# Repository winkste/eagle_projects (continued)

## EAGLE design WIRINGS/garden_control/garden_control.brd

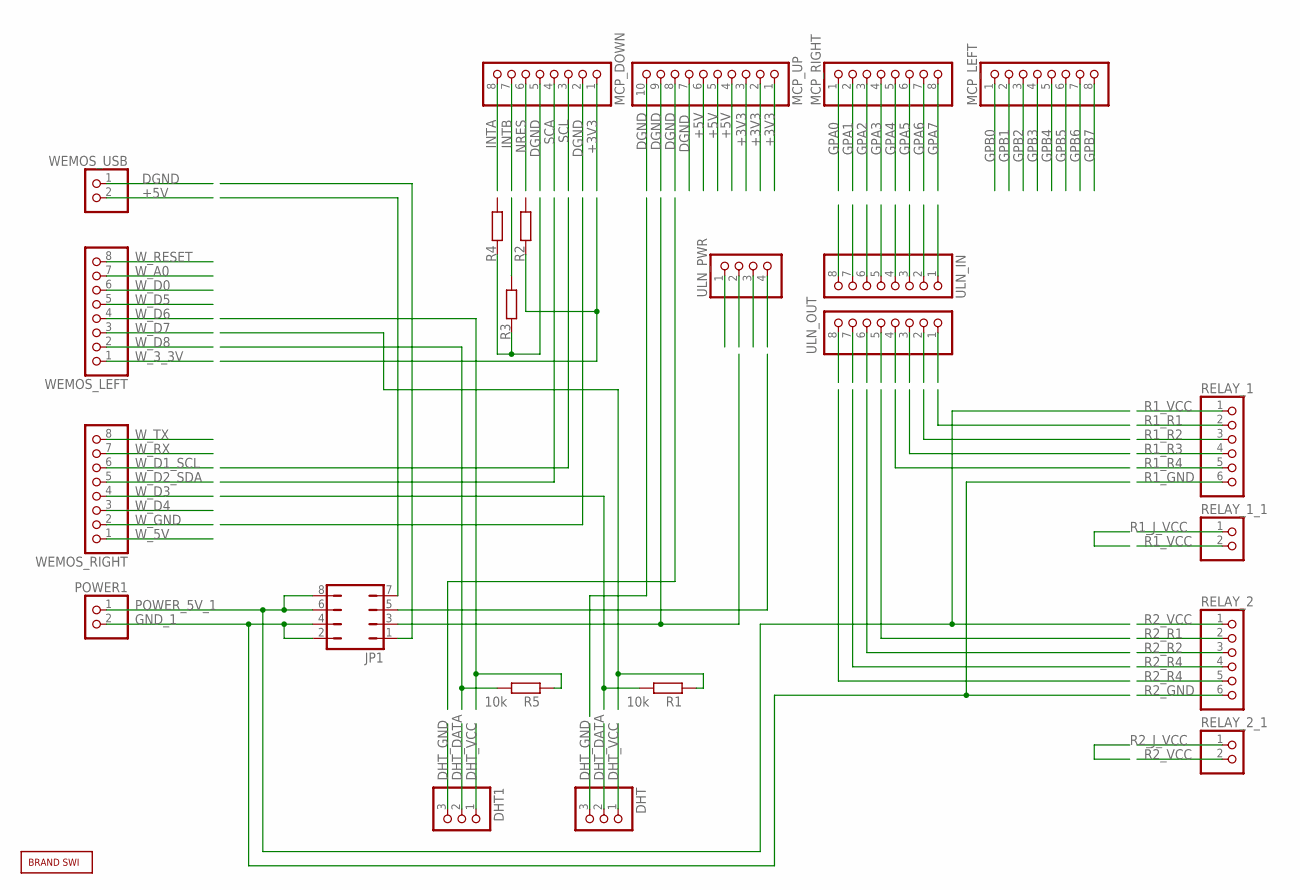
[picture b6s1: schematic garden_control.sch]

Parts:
DHT, DHT1: PINHD-1X3; 1X03
JP1: JP4Q
MCP_DOWN: PINHD-1X8; 1X08
MCP_LEFT: PINHD-1X8; 1X08
MCP_RIGHT: PINHD-1X8; 1X08
MCP_UP: PINHD-1X10; 1X10
POWER1: PINHD-1X2; 1X02
R1, R5: 10k; 0207/10
R2, R3, R4: R-EU_0204/7; 0204/7
RELAY_1, RELAY_2: PINHD-1X6; 1X06
RELAY_1_1, RELAY_2_1: PINHD-1X2; 1X02
U$2: BRAND_SWI5X7; BRAND_SWI_5X7
ULN_IN: PINHD-1X8; 1X08
ULN_OUT: PINHD-1X8; 1X08
ULN_PWR: PINHD-1X4; 1X04
WEMOS_LEFT: PINHD-1X8; 1X08
WEMOS_RIGHT: PINHD-1X8; 1X08
WEMOS_USB: PINHD-1X2; 1X02

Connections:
+3V3: MCP_DOWN.1, MCP_UP.1, MCP_UP.2, MCP_UP.3
+5V: MCP_UP.5, MCP_UP.6, WEMOS_USB.2
DGND: MCP_DOWN.2, MCP_DOWN.5, MCP_UP.8, MCP_UP.9, MCP_UP.10, WEMOS_USB.1
DHT_DATA: DHT.2, DHT1.2
DHT_GND: DHT.3, DHT1.3
DHT_VCC: DHT.1, DHT1.1
GND_1: JP1.2, JP1.4, POWER1.2
GPA0: MCP_RIGHT.1
GPA1: MCP_RIGHT.2
GPA2: MCP_RIGHT.3
GPA3: MCP_RIGHT.4
GPA4: MCP_RIGHT.5
GPA5: MCP_RIGHT.6
GPA6: MCP_RIGHT.7
GPA7: MCP_RIGHT.8
GPB0: MCP_LEFT.1
GPB1: MCP_LEFT.2
GPB2: MCP_LEFT.3
GPB3: MCP_LEFT.4
GPB4: MCP_LEFT.5
GPB5: MCP_LEFT.6
GPB6: MCP_LEFT.7
GPB7: MCP_LEFT.8
INTA: MCP_DOWN.8
INTB: MCP_DOWN.7
unnamed: R3.1, R4.1
NRES: MCP_DOWN.6
POWER_5V_1: JP1.6, JP1.8, POWER1.1
R1_GND: RELAY_1.6
R1_J_VCC: RELAY_1_1.1
R1_R1: RELAY_1.2
R1_R2: RELAY_1.3
R1_R3: RELAY_1.4
R1_R4: RELAY_1.5
R1_VCC: RELAY_1.1, RELAY_1_1.2
R2_GND: RELAY_2.6
R2_J_VCC: RELAY_2_1.1
R2_R1: RELAY_2.2
R2_R2: RELAY_2.3
R2_R4: RELAY_2.4, RELAY_2.5
R2_VCC: RELAY_2.1, RELAY_2_1.2
SCA: MCP_DOWN.4
SCL: MCP_DOWN.3
W_3_3V: WEMOS_LEFT.1
W_5V: WEMOS_RIGHT.1
W_A0: WEMOS_LEFT.7
W_D0: WEMOS_LEFT.6
W_D1_SCL: WEMOS_RIGHT.6
W_D2_SDA: WEMOS_RIGHT.5
W_D3: WEMOS_RIGHT.4
W_D4: WEMOS_RIGHT.3
W_D5: WEMOS_LEFT.5
W_D6: WEMOS_LEFT.4
W_D7: WEMOS_LEFT.3
W_D8: WEMOS_LEFT.2
W_GND: WEMOS_RIGHT.2
W_RESET: WEMOS_LEFT.8
W_RX: WEMOS_RIGHT.7
W_TX: WEMOS_RIGHT.8

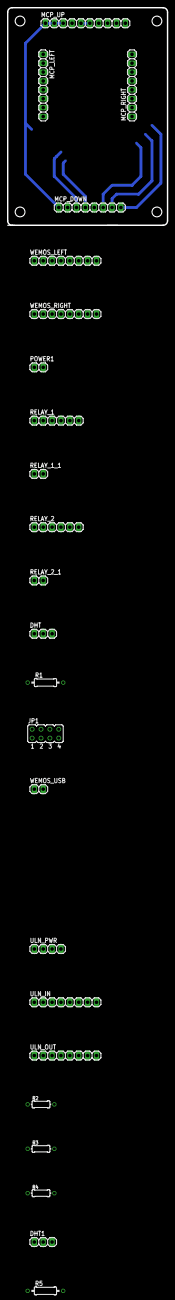
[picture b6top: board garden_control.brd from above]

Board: 2 copper layers, 45.7 x 62.2 mm, 24 parts (1 on the bottom side), 12 nets.

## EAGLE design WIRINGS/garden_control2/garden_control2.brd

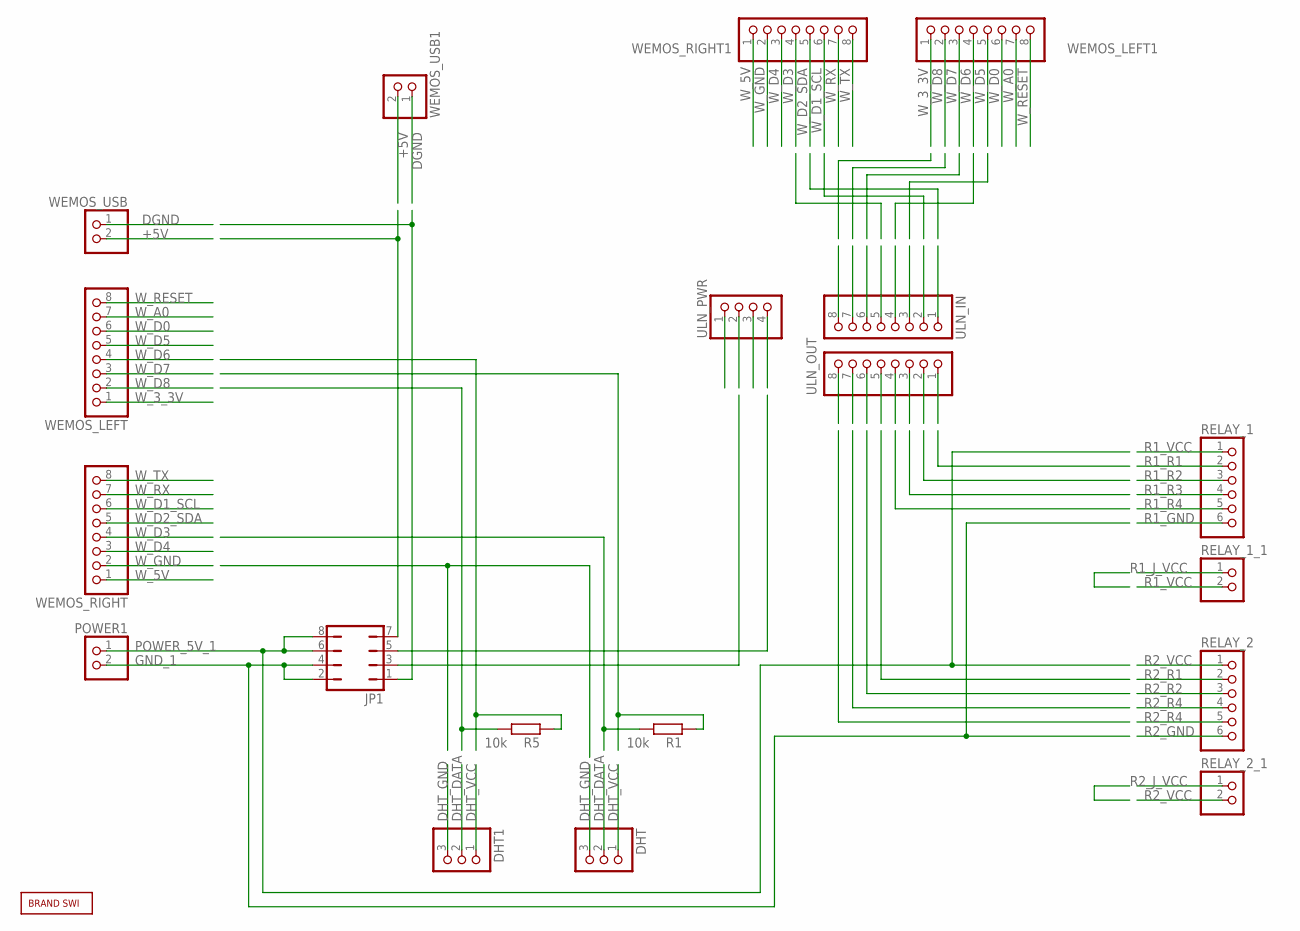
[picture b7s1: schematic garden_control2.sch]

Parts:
DHT, DHT1: PINHD-1X3; 1X03
JP1: JP4Q
POWER1: PINHD-1X2; 1X02
R1, R5: 10k; 0207/10
RELAY_1, RELAY_2: PINHD-1X6; 1X06
RELAY_1_1, RELAY_2_1: PINHD-1X2; 1X02
U$2: BRAND_SWI5X7; BRAND_SWI_5X7
ULN_IN: PINHD-1X8; 1X08
ULN_OUT: PINHD-1X8; 1X08
ULN_PWR: PINHD-1X4; 1X04
WEMOS_LEFT, WEMOS_LEFT1: PINHD-1X8; 1X08
WEMOS_RIGHT, WEMOS_RIGHT1: PINHD-1X8; 1X08
WEMOS_USB, WEMOS_USB1: PINHD-1X2; 1X02

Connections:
+5V: WEMOS_USB.2, WEMOS_USB1.2
DGND: WEMOS_USB.1, WEMOS_USB1.1
DHT_DATA: DHT.2, DHT1.2
DHT_GND: DHT.3, DHT1.3
DHT_VCC: DHT.1, DHT1.1
GND_1: JP1.2, JP1.4, POWER1.2
POWER_5V_1: JP1.6, JP1.8, POWER1.1
R1_GND: RELAY_1.6
R1_J_VCC: RELAY_1_1.1
R1_R1: RELAY_1.2
R1_R2: RELAY_1.3
R1_R3: RELAY_1.4
R1_R4: RELAY_1.5
R1_VCC: RELAY_1.1, RELAY_1_1.2
R2_GND: RELAY_2.6
R2_J_VCC: RELAY_2_1.1
R2_R1: RELAY_2.2
R2_R2: RELAY_2.3
R2_R4: RELAY_2.4, RELAY_2.5
R2_VCC: RELAY_2.1, RELAY_2_1.2
W_3_3V: WEMOS_LEFT.1, WEMOS_LEFT1.1
W_5V: WEMOS_RIGHT.1, WEMOS_RIGHT1.1
W_A0: WEMOS_LEFT.7, WEMOS_LEFT1.7
W_D0: WEMOS_LEFT.6, WEMOS_LEFT1.6
W_D1_SCL: WEMOS_RIGHT.6, WEMOS_RIGHT1.6
W_D2_SDA: WEMOS_RIGHT.5, WEMOS_RIGHT1.5
W_D3: WEMOS_RIGHT.4, WEMOS_RIGHT1.4
W_D4: WEMOS_RIGHT.3, WEMOS_RIGHT1.3
W_D5: WEMOS_LEFT.5, WEMOS_LEFT1.5
W_D6: WEMOS_LEFT.4, WEMOS_LEFT1.4
W_D7: WEMOS_LEFT.3, WEMOS_LEFT1.3
W_D8: WEMOS_LEFT.2, WEMOS_LEFT1.2
W_GND: WEMOS_RIGHT.2, WEMOS_RIGHT1.2
W_RESET: WEMOS_LEFT.8, WEMOS_LEFT1.8
W_RX: WEMOS_RIGHT.7, WEMOS_RIGHT1.7
W_TX: WEMOS_RIGHT.8, WEMOS_RIGHT1.8

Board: 2 copper layers, 20 parts (1 on the bottom side), 26 nets, no tracks yet.
